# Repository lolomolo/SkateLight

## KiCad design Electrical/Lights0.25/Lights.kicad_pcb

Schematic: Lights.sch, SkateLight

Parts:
BT1, BT2, BT3, BT4: 54; Manufacturer_Part_Number 54; Mouser Part Number 534-54
C1, C2, C4, C6, C9: 4.7uF; C_0805_HandSoldering
C3, C5, C7, C8, C10: .1uF; C_0805_HandSoldering
D1, D2, D3, D4, D5, D6, D9, D10, D11, D12, D13, D14, D15, D16, D17, D18, D19, D20, D21, D22: LED; LED_1206
IC1, IC2, IC3: STP08DP05XTTR; SOP65P640X120-17N; Manufacturer_Part_Number STP08DP05XTTR
J1, J2, J3, J4, J5, J6: Conn_01x10_Male; HDRV10W40P127_1X10_400X210X550P
J7: Conn_01x06_Male; Molex_SPOX-5267_22-03-5065_06x2.54mm_Straight
J12: Conn_01x07_Male; Molex_SPOX-5267_22-03-5075_07x2.54mm_Straight
R1, R2, R3: 370; R_0805_HandSoldering
U1: AZ1117-3.3; SOT-223-3_TabPin2

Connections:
+3V3: C9.1, C10.1, IC1.16, IC2.16, IC3.16, J12.7, U1.2 (VO)
CLK: IC1.3, IC2.3, IC3.3, J12.4
GND: BT4.1, BT4.2, BT4.3, C1.2, C2.2, C3.2, C4.2, C5.2, C6.2, C7.2, C8.2, C9.2, C10.2, IC1.1, IC1.17, IC2.1, IC2.17, IC3.1, IC3.17, J7.1, J7.2, J12.1, R1.1, R2.1, R3.1, U1.1 (GND)
LE: IC1.4, IC2.4, IC3.4, J12.6
MID: BT2.1, BT2.2, BT2.3, BT3.1, BT3.2, BT3.3, J7.5
unnamed: D1.1, J2.2
unnamed: D1.2, D2.2, D3.2, D4.2, D5.2, D6.2, J2.1, J2.10
unnamed: D2.1, J2.3
unnamed: D3.1, J2.4
unnamed: D4.1, J2.5
unnamed: D5.1, J2.6
unnamed: D6.1, J2.7
unnamed: D9.1, J4.2
unnamed: D10.1, J4.3
unnamed: D9.2, D10.2, D11.2, D12.2, D13.2, D14.2, D15.2, D16.2, J4.1, J4.10
unnamed: D11.1, J4.4
unnamed: D12.1, J4.5
unnamed: D13.1, J4.6
unnamed: D14.1, J4.7
unnamed: D15.1, J4.8
unnamed: D16.1, J4.9
unnamed: D17.1, J6.2
unnamed: D17.2, D18.2, D19.2, D20.2, D21.2, D22.2, J6.1, J6.10
unnamed: D18.1, J6.3
unnamed: D19.1, J6.4
unnamed: D20.1, J6.5
unnamed: D21.1, J6.6
unnamed: D22.1, J6.7
unnamed: IC1.5, J1.2
unnamed: IC1.6, J1.3
unnamed: IC1.7, J1.4
unnamed: IC1.8, J1.5
unnamed: IC1.9, J1.6
unnamed: IC1.10, J1.7
unnamed: IC1.11, J1.8
unnamed: IC1.12, J1.9
unnamed: IC1.14, IC2.2
unnamed: IC1.15, R1.2
unnamed: IC2.5, J3.2
unnamed: IC2.6, J3.3
unnamed: IC2.7, J3.4
unnamed: IC2.8, J3.5
unnamed: IC2.9, J3.6
unnamed: IC2.10, J3.7
unnamed: IC2.11, J3.8
unnamed: IC2.12, J3.9
unnamed: IC2.14, IC3.2
unnamed: IC2.15, R2.2
unnamed: IC3.5, J5.9
unnamed: IC3.6, J5.8
unnamed: IC3.7, J5.7
unnamed: IC3.8, J5.6
unnamed: IC3.9, J5.5
unnamed: IC3.10, J5.4
unnamed: IC3.11, J5.3
unnamed: IC3.12, J5.2
unnamed: IC3.15, R3.2
OE: IC1.13, IC2.13, IC3.13, J12.5
SDA: IC1.2, J12.3
SDO: IC3.14, J12.2
VBat: BT1.1, BT1.2, BT1.3, C1.1, C8.1, J7.6, U1.3 (VI)
VCC: C2.1, C3.1, C4.1, C5.1, C6.1, C7.1, J1.1, J1.10, J3.1, J3.10, J5.1, J5.10, J7.3, J7.4

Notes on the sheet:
60mA*20=1.2A
Forward voltage 2.85v

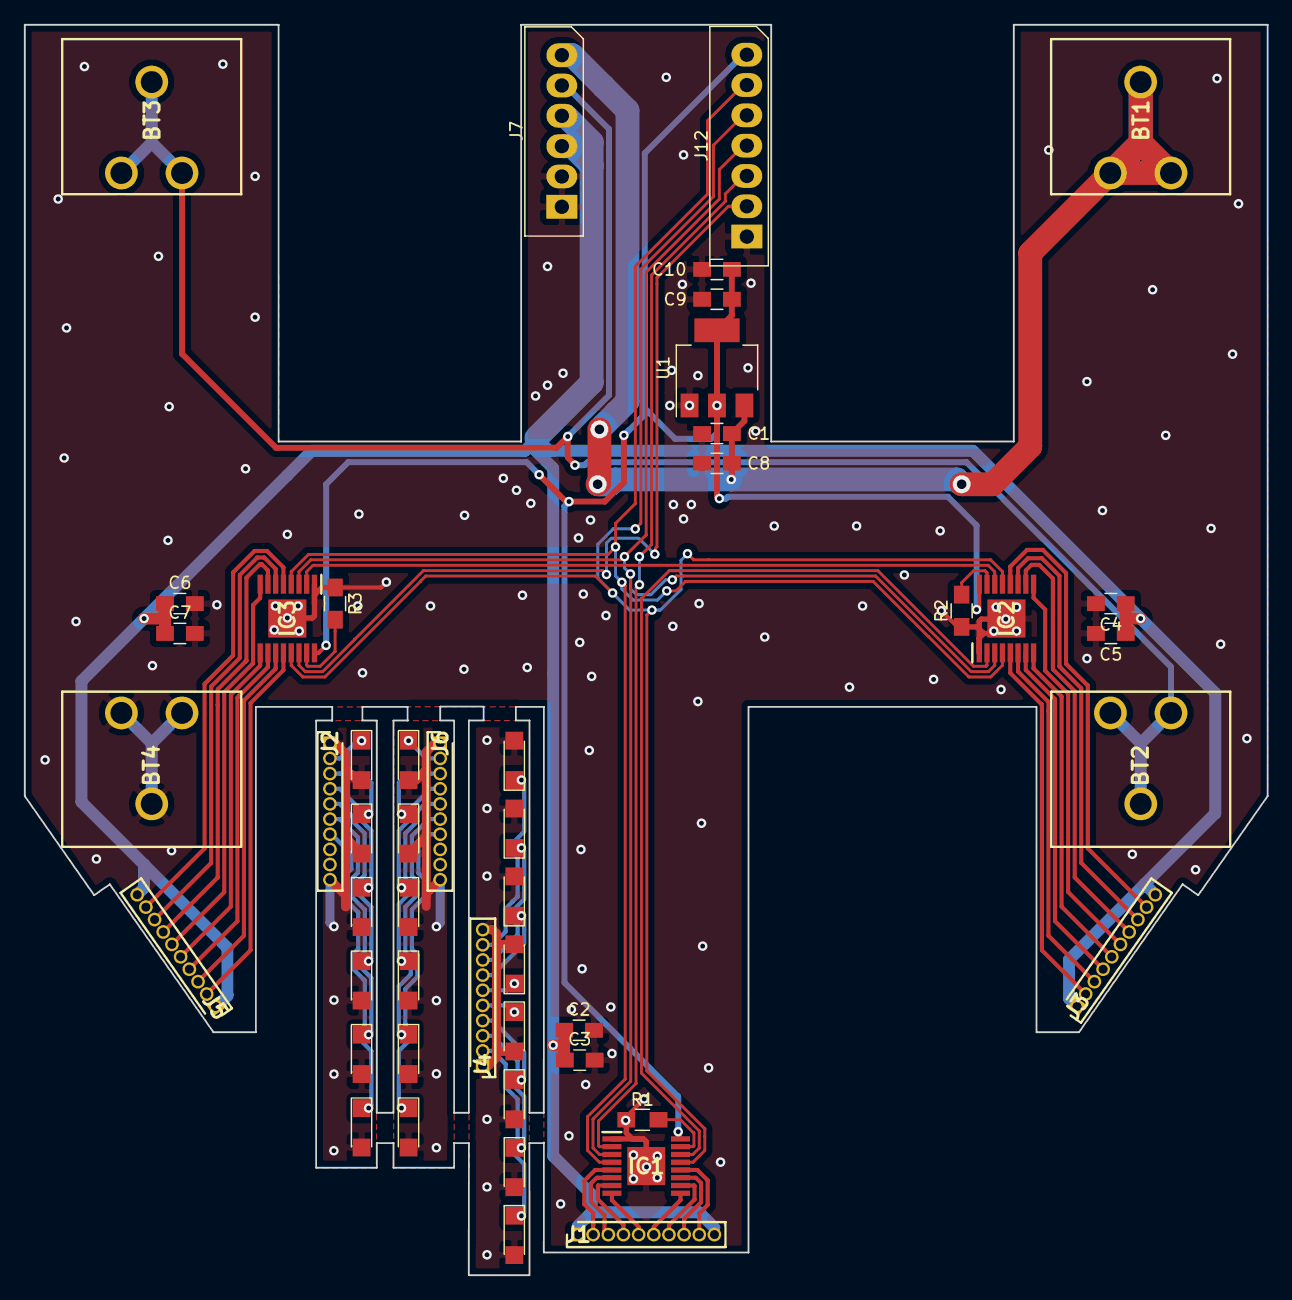
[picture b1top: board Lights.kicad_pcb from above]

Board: 2 copper layers, 104.1 x 104.8 mm, 49 parts (0 on the bottom side), 62 nets.

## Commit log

2018-12-05 init
2018-12-13 single chip replacement start
2019-01-08 pcb 0.25 rolled out
